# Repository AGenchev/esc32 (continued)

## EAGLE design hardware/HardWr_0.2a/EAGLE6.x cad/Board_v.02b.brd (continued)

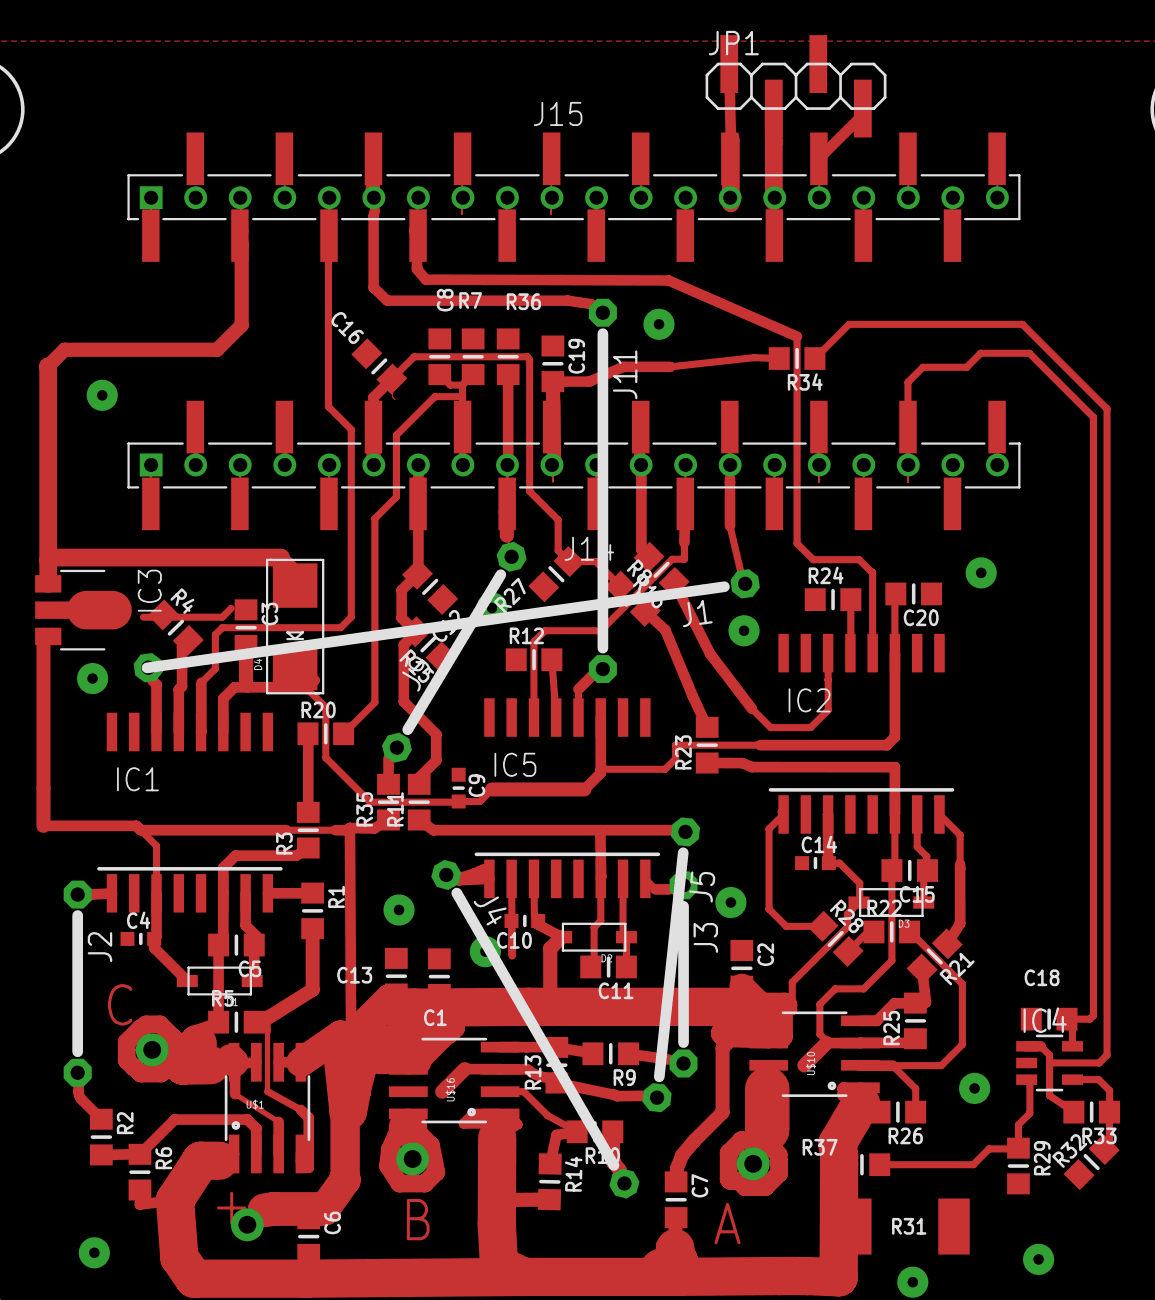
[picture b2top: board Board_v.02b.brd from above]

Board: 2 copper layers, 83 parts (0 on the bottom side), 76 nets.

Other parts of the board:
U$11, U$12, U$13, U$21: MOUNTINGHOLE_2.8

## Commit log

2017-11-25 Different makefile
    Compiles the ESC firmware with a GNU arm-none-eabi toolchain.
2017-11-25 Rename onboard/adc.c to onboard/src/adc.c
2017-11-25 Rename onboard/adc.h to onboard/src/adc.h
2017-11-25 Refactoring of the project to have cleaner layout
2017-11-25 Refactoring
2017-11-25 Code rework. Add all necessary routines to compile w GCC
2018-02-25 Create empty
2018-02-25 Update Readme.md
    added hardware schematics
2018-02-25 Update README.md
    fixed typo
2018-03-01 Update README.md
    reflect things as of 1 March 2018
2018-03-01 Synced code with my latest experiments
2018-03-03 Update Makefile
